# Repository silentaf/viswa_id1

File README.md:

# VisionAid: Vishwakarma Awards 2026–27 (Team SVNIT)

A chest-worn, fully offline navigation aid for blind and low-vision users that **adds head-level-obstacle and drop-off warnings to the white cane**.
- An **FPGA safety island** (Tang Nano 9K) keeps the alert path running even if the AI computer fails.
- An on-device AI layer (Raspberry Pi 5) names hazards and reads text aloud.

**Stage 2: Design Development.** This repository holds the design files. Nothing has been fabricated yet. Every number is labelled *target*, *calculated*, *simulated*, *cited* or *measured on the development laptop* (Pi software, not a Pi 5); none is a measurement on VisionAid hardware.

| Path | Contents |
|---|---|
| [`VisionAid_Proposal_v2.md`](VisionAid_Proposal_v2.md) | Design specification v2: the Stage 1 proposal corrected, with every change explained |
| [`IMPLEMENTATION_PLAN.md`](IMPLEMENTATION_PLAN.md) | Stage 2 plan, gates, slide map, checklist |
| [`design/electronics/`](design/electronics/) | KiCad 9 carrier board: schematic, PCB, Gerbers, BOM, STEP (ERC 0 / DRC 0) |
| [`design/fpga/`](design/fpga/) | Verilog safety island, testbench (all tests pass), waveforms, Yosys utilisation |
| [`design/cad/`](design/cad/) | FreeCAD parametric chest pod, STEP/STL, renders, mount FEA |
| [`design/bom/`](design/bom/) | Prototype BOM and power budget (xlsx) |

All design files are generated by the scripts in each folder (`scripts/`), so every design decision is written down and reproducible. See [`design/README.md`](design/README.md) for the tools and how to open each file.

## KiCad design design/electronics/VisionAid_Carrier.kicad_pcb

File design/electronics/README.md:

# VisionAid Carrier Board: Electronics Design (v0.1, design stage)

**Status (8 Oct 2026):**
- **Designed and verified in KiCad 9:** ERC 0 violations; DRC 0 violations; 0 unconnected; schematic ↔ PCB parity 0 issues.
- **Not fabricated or tested yet.** Every number below is a design value or target, not a measurement.

## What this board does

It is the **interface and safety-island board** that sits on top of the Raspberry Pi 5 in the chest pod.

| Block | Parts | Why it is designed this way |
|---|---|---|
| **FPGA safety island** | U1 Sipeed Tang Nano 9K (GW1NR-9, 27 MHz) on 2 × 24 sockets | Times all 3 ultrasonic echoes **in parallel** and drives the motors **without the Pi**. If Linux or the AI crashes, obstacle alerts continue (watchdog on `PI_HB`). Only **3.3 V-bank pins** on the left header are used; the right-header pins marked `_1V8` are on a 1.8 V bank and are unused. |
| **Pi link** | J1 2 × 20 header → 40-way IDC ribbon → Pi GPIO | UART (GPIO14/15) for status and config, GPIO17 = heartbeat to the FPGA, GPIO27 = fault from the FPGA, I²C (GPIO2/3) for the IMU. |
| **Power** | F1 500 mA PTC, U2 AMS1117-3.3, C1–C5, D1 SS14 | 5 V comes from the Pi header (the Pi is powered by a BIS-certified USB-C power bank). The PTC protects the Pi's 5 V rail if this board shorts. A separate 3.3 V regulator means the Pi's 3.3 V pins (1, 17) are deliberately **not** used. D1 stops back-feed when the Tang Nano's own USB-C is plugged in for programming. |
| **Sensors** | J2–J4 RCWL-1601 ultrasonic (left, right, head-level), J5 TF-Luna LiDAR (drop-offs), J8 MPU-6050 IMU | RCWL-1601 works at 3.3 V, so there is no level shifting. The TF-Luna takes 5 V but has 3.3 V UART logic. 100 Ω series resistors (R7–R14) limit fault current and ringing on the cables. |
| **Haptics and alarm** | Q1–Q3 AO3400A, R1–R6, D2–D4, J6/J7 coin motors, BZ1 buzzer | Logic-level MOSFETs (V_GS(th) ≤ 1.45 V) are switched directly by the FPGA's 3.3 V PWM. 100 kΩ pull-downs keep the motors off while the FPGA boots. Flyback diodes protect the MOSFETs. The motors (3 V coin ERMs) run from +3V3. |
| **Buttons** | J9 (READ = OCR, MODE, QUIET), R15–R17 10 k pull-ups, C7–C9 100 nF | 10 k × 100 nF ≈ 1 ms RC filter, plus digital debounce in the FPGA. |
| **Test points** | TP1–TP6 (+5V, +3V3, GND, US_L_ECHO, MOT_L_G, PI_HB) | For the Stage 3 logic-analyser measurement of **echo → motor-on latency** and for power checks. |

## FPGA pin map (Tang Nano 9K, 3.3 V banks only)

| Signal | FPGA pin | Signal | FPGA pin |
|---|---|---|---|
| US_L_TRIG / ECHO | 25 / 26 | PI_TXD (FPGA RX) / PI_RXD (FPGA TX) | 40 / 35 |
| US_R_TRIG / ECHO | 27 / 28 | PI_HB (heartbeat in) | 41 |
| US_H_TRIG / ECHO | 29 / 30 | FPGA_FAULT_N (out to Pi) | 42 |
| LIDAR_TX / LIDAR_RX | 33 / 34 | MOT_L_PWM / MOT_R_PWM / BUZZ_EN | 51 / 53 / 54 |
| Clock 27 MHz (on module) | 52 | BTN_READ / MODE / QUIET | 55 / 56 / 57 |

Source: the Sipeed Tang Nano 9K official pin map (wiki.sipeed.com).

## PCB

- **Outline:** 85 × 56 mm, 2 layers, 1.6 mm FR-4. It has the **same outline and M2.5 mounting holes as the Raspberry Pi 5**, and is stacked above the Pi on **20 mm standoffs**. Those clear the Pi's USB/Ethernet jacks and the active cooler; a standard HAT would hit them.
- **Layout:**
  - The Tang Nano sits on 8.5 mm sockets, with its USB-C flush at the right edge for programming.
  - Low-profile SMD parts sit **under** the module, between the socket rows.
  - Sensor connectors are on the bottom edge (cables exit downward towards the sensor windows). Buttons, IMU and motor connectors are on the left edge.
- **Track rules:**
  - 5 V and GND: 0.5 mm.
  - +3V3: 0.3 mm (about 250 mA total load).
  - Signals: 0.25 mm (minimum 0.15 mm, where the router necks down at pads).
  - Clearance 0.2 mm; vias 0.6/0.3 mm.
  - GND pours on both layers.
- **Routing:** FreeRouting v2.5.0 completed 100 %, with 0 violations.

## How the files are produced (reproducible)

All files are generated from scripts so every design decision is written down:

```
tools/kicad.sh python design/electronics/scripts/gen_library.py    # Tang Nano symbol + footprint
python3 design/electronics/scripts/gen_schematic.py                # schematic (.kicad_sch)
tools/kicad.sh kicad-cli sch export netlist -o design/electronics/VisionAid_Carrier.net design/electronics/VisionAid_Carrier.kicad_sch
tools/kicad.sh python design/electronics/scripts/gen_pcb.py        # outline, placement, nets
tools/kicad.sh python design/electronics/scripts/route_pcb.py      # FreeRouting + GND pours
```

Open the project in the KiCad GUI with `tools/kicad.sh kicad design/electronics/VisionAid_Carrier.kicad_pro`.

## Outputs (`outputs/`)

| File | Contents |
|---|---|
| `VisionAid_Carrier_schematic.pdf` / `.svg` | Schematic |
| `VisionAid_Carrier_pcb_top.pdf` / `_bottom.pdf` | Copper and silkscreen plots |
| `gerbers/` | Fabrication files (Gerber X2 + Excellon drill + drill map) |
| `VisionAid_Carrier_BOM.csv` | Bill of materials (on-board parts) |
| `VisionAid_Carrier_pos.csv` | Pick-and-place positions |
| `VisionAid_Carrier.step` | 3D model for the enclosure CAD |
| `pcb_3d_top.png` / `pcb_3d_iso.png` | Board renders with component 3D models (Tang Nano 9K: simplified model in `3d/`) |
| `ERC_report.txt` / `DRC_report.txt` | Verification reports |

## Not on the PCB BOM (buy separately in Stage 3)

- 2 × 1×24 female headers (2.54 mm, 8.5 mm tall) for the Tang Nano.
- 40-way IDC ribbon cable with 2 sockets (≈ 10 cm).
- 4 × M2.5 × 20 mm standoffs and screws.
- JST-XH housings and crimps.
- The sensors, motors and buttons themselves (see the implementation plan, §5).

## Open items before fabrication (Stage 3)

1. **Measure the Tang Nano 9K header row spacing with calipers.** The footprint uses 22.86 mm (0.9″), taken from a community footprint, not an official drawing.
2. Confirm the ribbon length and the standoff height against the enclosure CAD.
3. Check the AMS1117 dropout and temperature at the real load: 5 V → 3.3 V at ~250 mA ≈ 0.43 W in SOT-223.
4. Review the board in the KiCad GUI: tidy silkscreen, then re-run DRC.

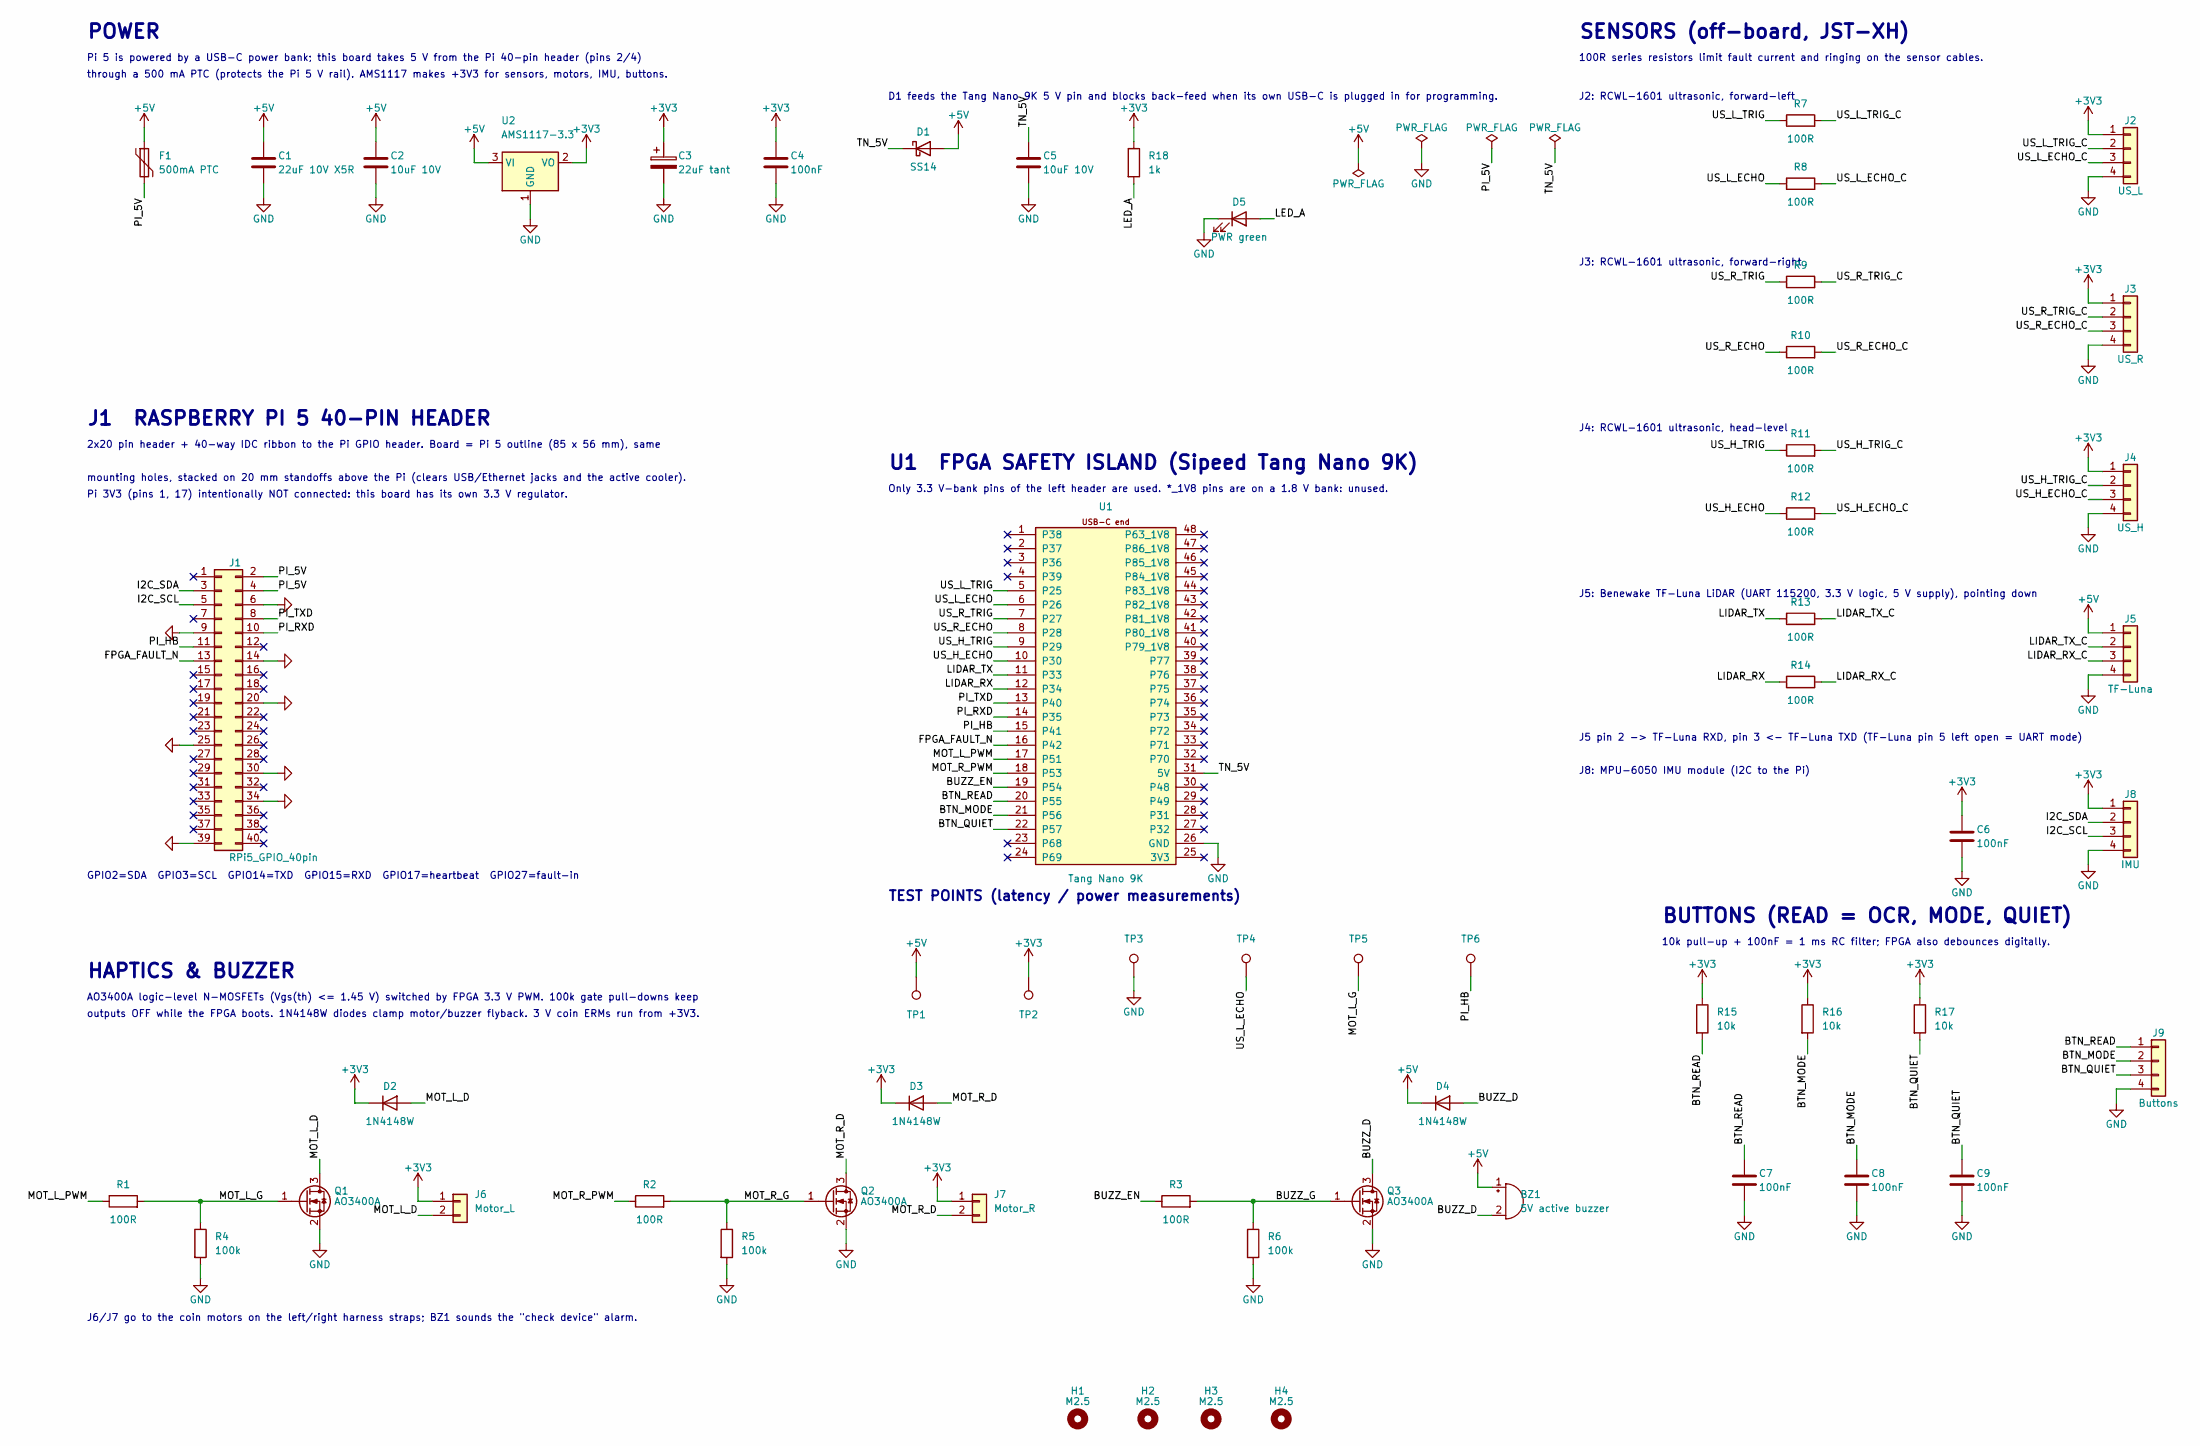
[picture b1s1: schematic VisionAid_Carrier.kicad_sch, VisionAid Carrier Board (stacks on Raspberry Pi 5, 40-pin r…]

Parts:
BZ1: 5V active buzzer; Buzzer_12x9.5RM7.6; MPN 12 mm 5 V active buzzer
C1: 22uF 10V X5R; C_1206_3216Metric
C2, C5: 10uF 10V; C_0805_2012Metric
C3: 22uF tant; CP_EIA-3528-21_Kemet-B
C4, C6, C7, C8, C9: 100nF; C_0603_1608Metric
D1: SS14; D_SMA; MPN SS14
D2, D3, D4: 1N4148W; D_SOD-123; MPN 1N4148W
D5: PWR green; LED_0603_1608Metric
F1: 500mA PTC; Fuse_1206_3216Metric; MPN 1206L050 / equivalent
H1, H2, H3, H4: M2.5; MountingHole_2.7mm_M2.5
J1: RPi5_GPIO_40pin; PinHeader_2x20_P2.54mm_Vertical
J2: US_L; JST_XH_B4B-XH-A_1x04_P2.50mm_Vertical; MPN JST B4B-XH-A
J3: US_R; JST_XH_B4B-XH-A_1x04_P2.50mm_Vertical; MPN JST B4B-XH-A
J4: US_H; JST_XH_B4B-XH-A_1x04_P2.50mm_Vertical; MPN JST B4B-XH-A
J5: TF-Luna; JST_XH_B4B-XH-A_1x04_P2.50mm_Vertical; MPN JST B4B-XH-A
J6: Motor_L; JST_XH_B2B-XH-A_1x02_P2.50mm_Vertical; MPN JST B2B-XH-A
J7: Motor_R; JST_XH_B2B-XH-A_1x02_P2.50mm_Vertical; MPN JST B2B-XH-A
J8: IMU; JST_XH_B4B-XH-A_1x04_P2.50mm_Vertical; MPN JST B4B-XH-A
J9: Buttons; JST_XH_B4B-XH-A_1x04_P2.50mm_Vertical; MPN JST B4B-XH-A
Q1, Q2, Q3: AO3400A; SOT-23; MPN AO3400A
R1, R2, R3, R7, R8, R9, R10, R11, R12, R13, R14: 100R; R_0603_1608Metric
R4, R5, R6: 100k; R_0603_1608Metric
R15, R16, R17: 10k; R_0603_1608Metric
R18: 1k; R_0603_1608Metric
TP1: +5V; TestPoint_Pad_D1.5mm
TP2: +3V3; TestPoint_Pad_D1.5mm
TP3: GND; TestPoint_Pad_D1.5mm
TP4: US_L_ECHO; TestPoint_Pad_D1.5mm
TP5: MOT_L_G; TestPoint_Pad_D1.5mm
TP6: PI_HB; TestPoint_Pad_D1.5mm
U1: Tang Nano 9K; TangNano9K_Module; MPN Sipeed Tang Nano 9K
U2: AMS1117-3.3; SOT-223-3_TabPin2; MPN AMS1117-3.3

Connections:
+3V3: C3.1, C4.1, C6.1, D2.1 (K), D3.1 (K), J2.1, J3.1, J4.1, J6.1, J7.1, J8.1, R15.1, R16.1, R17.1, R18.1, TP2.1, U2.2 (VO)
+5V: BZ1.1 (+), C1.1, C2.1, D1.2 (A), D4.1 (K), F1.1, J5.1, TP1.1, U2.3 (VI)
/BTN_MODE: C8.1, J9.2, R16.2, U1.21 (P56)
/BTN_QUIET: C9.1, J9.3, R17.2, U1.22 (P57)
/BTN_READ: C7.1, J9.1, R15.2, U1.20 (P55)
/BUZZ_D: BZ1.2 (-), D4.2 (A), Q3.3 (D)
/BUZZ_EN: R3.1, U1.19 (P54)
/BUZZ_G: Q3.1 (G), R3.2, R6.1
/FPGA_FAULT_N: J1.13, U1.16 (P42)
/I2C_SCL: J1.5, J8.3
/I2C_SDA: J1.3, J8.2
/LED_A: D5.2 (A), R18.2
/LIDAR_RX: R14.1, U1.12 (P34)
/LIDAR_RX_C: J5.3, R14.2
/LIDAR_TX: R13.1, U1.11 (P33)
/LIDAR_TX_C: J5.2, R13.2
/MOT_L_D: D2.2 (A), J6.2, Q1.3 (D)
/MOT_L_G: Q1.1 (G), R1.2, R4.1, TP5.1
/MOT_L_PWM: R1.1, U1.17 (P51)
/MOT_R_D: D3.2 (A), J7.2, Q2.3 (D)
/MOT_R_G: Q2.1 (G), R2.2, R5.1
/MOT_R_PWM: R2.1, U1.18 (P53)
/PI_5V: F1.2, J1.2, J1.4
/PI_HB: J1.11, TP6.1, U1.15 (P41)
/PI_RXD: J1.10, U1.14 (P35)
/PI_TXD: J1.8, U1.13 (P40)
/TN_5V: C5.1, D1.1 (K), U1.31 (5V)
/US_H_ECHO: R12.1, U1.10 (P30)
/US_H_ECHO_C: J4.3, R12.2
/US_H_TRIG: R11.1, U1.9 (P29)
/US_H_TRIG_C: J4.2, R11.2
/US_L_ECHO: R8.1, TP4.1, U1.6 (P26)
/US_L_ECHO_C: J2.3, R8.2
/US_L_TRIG: R7.1, U1.5 (P25)
/US_L_TRIG_C: J2.2, R7.2
/US_R_ECHO: R10.1, U1.8 (P28)
/US_R_ECHO_C: J3.3, R10.2
/US_R_TRIG: R9.1, U1.7 (P27)
/US_R_TRIG_C: J3.2, R9.2
GND: C1.2, C2.2, C3.2, C4.2, C5.2, C6.2, C7.2, C8.2, C9.2, D5.1 (K), J1.6, J1.9, J1.14, J1.20, J1.25, J1.30, J1.34, J1.39, J2.4, J3.4, J4.4, J5.4, J8.4, J9.4, Q1.2 (S), Q2.2 (S), Q3.2 (S), R4.2, R5.2, R6.2, TP3.1, U1.26 (GND), U2.1 (GND)

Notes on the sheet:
POWER
Pi 5 is powered by a USB-C power bank; this board takes 5 V from the Pi 40-pin header (pins 2/4)
through a 500 mA PTC (protects the Pi 5 V rail). AMS1117 makes +3V3 for sensors, motors, IMU, buttons.
D1 feeds the Tang Nano 9K 5 V pin and blocks back-feed when its own USB-C is plugged in for programming.
J1 RASPBERRY PI 5 40-PIN HEADER
2x20 pin header + 40-way IDC ribbon to the Pi GPIO header. Board = Pi 5 outline (85 x 56 mm), same
mounting holes, stacked on 20 mm standoffs above the Pi (clears USB/Ethernet jacks and the active cooler).
Pi 3V3 (pins 1, 17) intentionally NOT connected: this board has its own 3.3 V regulator.
GPIO2=SDA GPIO3=SCL GPIO14=TXD GPIO15=RXD GPIO17=heartbeat GPIO27=fault-in
U1 FPGA SAFETY ISLAND (Sipeed Tang Nano 9K)
Only 3.3 V-bank pins of the left header are used. *_1V8 pins are on a 1.8 V bank: unused.
SENSORS (off-board, JST-XH)
100R series resistors limit fault current and ringing on the sensor cables.
J2: RCWL-1601 ultrasonic, forward-left
J3: RCWL-1601 ultrasonic, forward-right
J4: RCWL-1601 ultrasonic, head-level
J5: Benewake TF-Luna LiDAR (UART 115200, 3.3 V logic, 5 V supply), pointing down
J5 pin 2 -> TF-Luna RXD, pin 3 <- TF-Luna TXD (TF-Luna pin 5 left open = UART mode)
J8: MPU-6050 IMU module (I2C to the Pi)
HAPTICS & BUZZER
AO3400A logic-level N-MOSFETs (Vgs(th) <= 1.45 V) switched by FPGA 3.3 V PWM. 100k gate pull-downs keep
outputs OFF while the FPGA boots. 1N4148W diodes clamp motor/buzzer flyback. 3 V coin ERMs run from +3V3.
J6/J7 go to the coin motors on the left/right harness straps; BZ1 sounds the "check device" alarm.
BUTTONS (READ = OCR, MODE, QUIET)
10k pull-up + 100nF = 1 ms RC filter; FPGA also debounces digitally.
TEST POINTS (latency / power measurements)

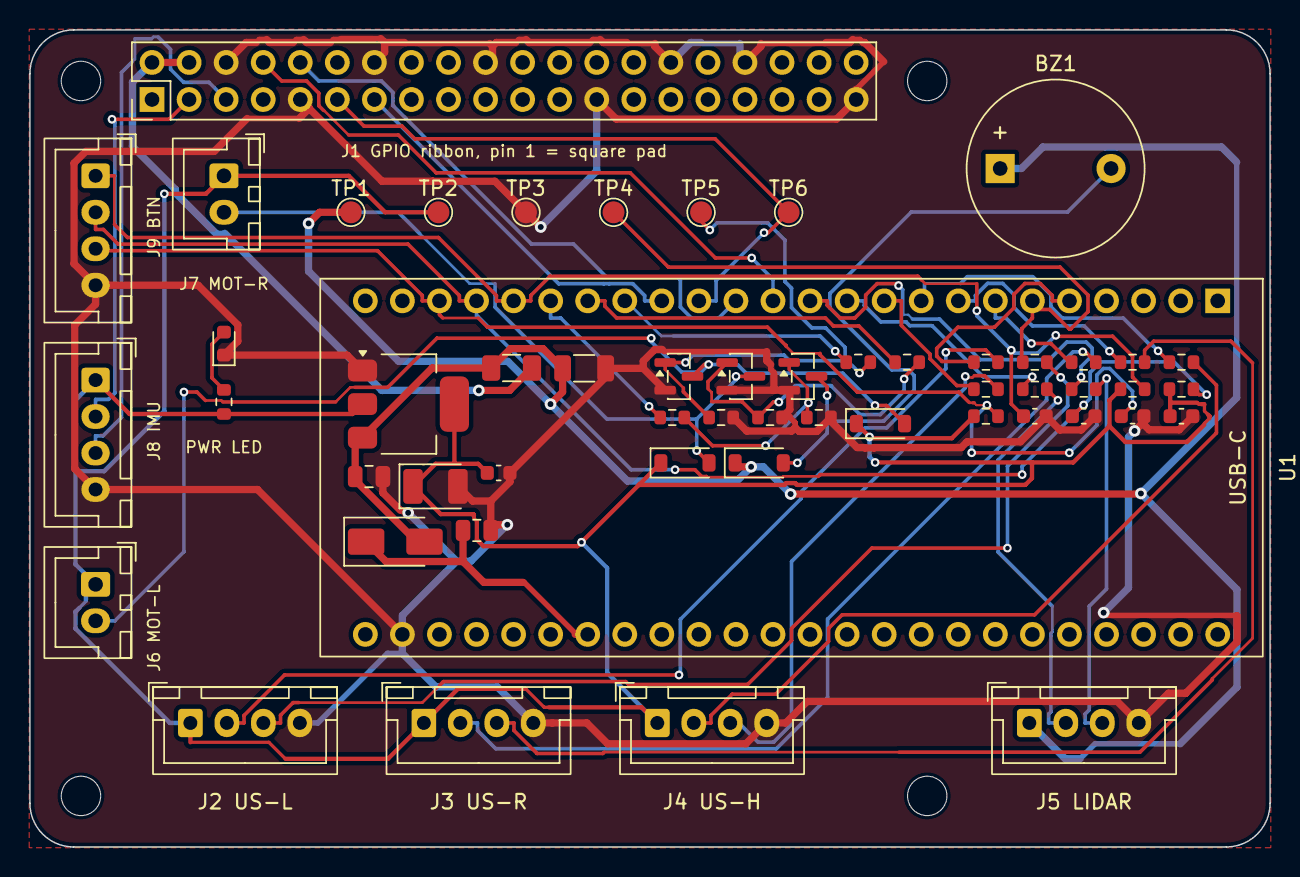
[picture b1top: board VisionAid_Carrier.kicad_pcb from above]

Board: 2 copper layers, 85.0 x 56.0 mm, 58 parts (0 on the bottom side), 40 nets.

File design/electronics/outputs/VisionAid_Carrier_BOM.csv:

"Refs","Value","Footprint","MPN","Qty"
"BZ1","5V active buzzer","Buzzer_Beeper:Buzzer_12x9.5RM7.6","12 mm 5 V active buzzer","1"
"C1","22uF 10V X5R","Capacitor_SMD:C_1206_3216Metric","","1"
"C2,C5","10uF 10V","Capacitor_SMD:C_0805_2012Metric","","2"
"C3","22uF tant","Capacitor_Tantalum_SMD:CP_EIA-3528-21_Kemet-B","","1"
"C4,C6,C7,C8,C9","100nF","Capacitor_SMD:C_0603_1608Metric","","5"
"D1","SS14","Diode_SMD:D_SMA","SS14","1"
"D2,D3,D4","1N4148W","Diode_SMD:D_SOD-123","1N4148W","3"
"D5","PWR green","LED_SMD:LED_0603_1608Metric","","1"
"F1","500mA PTC","Fuse:Fuse_1206_3216Metric","1206L050 / equivalent","1"
"J1","RPi5_GPIO_40pin","Connector_PinHeader_2.54mm:PinHeader_2x20_P2.54mm_Vertical","","1"
"J2","US_L","Connector_JST:JST_XH_B4B-XH-A_1x04_P2.50mm_Vertical","JST B4B-XH-A","1"
"J3","US_R","Connector_JST:JST_XH_B4B-XH-A_1x04_P2.50mm_Vertical","JST B4B-XH-A","1"
"J4","US_H","Connector_JST:JST_XH_B4B-XH-A_1x04_P2.50mm_Vertical","JST B4B-XH-A","1"
"J5","TF-Luna","Connector_JST:JST_XH_B4B-XH-A_1x04_P2.50mm_Vertical","JST B4B-XH-A","1"
"J6","Motor_L","Connector_JST:JST_XH_B2B-XH-A_1x02_P2.50mm_Vertical","JST B2B-XH-A","1"
"J7","Motor_R","Connector_JST:JST_XH_B2B-XH-A_1x02_P2.50mm_Vertical","JST B2B-XH-A","1"
"J8","IMU","Connector_JST:JST_XH_B4B-XH-A_1x04_P2.50mm_Vertical","JST B4B-XH-A","1"
"J9","Buttons","Connector_JST:JST_XH_B4B-XH-A_1x04_P2.50mm_Vertical","JST B4B-XH-A","1"
"Q1,Q2,Q3","AO3400A","Package_TO_SOT_SMD:SOT-23","AO3400A","3"
"R1,R2,R3,R7,R8,R9,R10,R11,R12,R13,R14","100R","Resistor_SMD:R_0603_1608Metric","","11"
"R4,R5,R6","100k","Resistor_SMD:R_0603_1608Metric","","3"
"R15,R16,R17","10k","Resistor_SMD:R_0603_1608Metric","","3"
"R18","1k","Resistor_SMD:R_0603_1608Metric","","1"
"U1","Tang Nano 9K","VisionAid:TangNano9K_Module","Sipeed Tang Nano 9K","1"
"U2","AMS1117-3.3","Package_TO_SOT_SMD:SOT-223-3_TabPin2","AMS1117-3.3","1"

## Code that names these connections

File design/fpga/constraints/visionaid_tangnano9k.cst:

// VisionAid safety island - Tang Nano 9K (GW1NR-LV9QN88PC6/I5) physical constraints.
// Pin numbers from the Sipeed Tang Nano 9K pin map; all user I/O on the 3.3 V banks (left header).
IO_LOC "clk" 52;
IO_PORT "clk" IO_TYPE=LVCMOS33 PULL_MODE=UP;
IO_LOC "rst_n" 4;
IO_PORT "rst_n" PULL_MODE=UP;  // on-board button S1
IO_LOC "us_trig[0]" 25;
IO_PORT "us_trig[0]" IO_TYPE=LVCMOS33 DRIVE=8;
IO_LOC "us_echo[0]" 26;
IO_PORT "us_echo[0]" IO_TYPE=LVCMOS33 PULL_MODE=DOWN;
IO_LOC "us_trig[1]" 27;
IO_PORT "us_trig[1]" IO_TYPE=LVCMOS33 DRIVE=8;
IO_LOC "us_echo[1]" 28;
IO_PORT "us_echo[1]" IO_TYPE=LVCMOS33 PULL_MODE=DOWN;
IO_LOC "us_trig[2]" 29;
IO_PORT "us_trig[2]" IO_TYPE=LVCMOS33 DRIVE=8;
IO_LOC "us_echo[2]" 30;
IO_PORT "us_echo[2]" IO_TYPE=LVCMOS33 PULL_MODE=DOWN;
IO_LOC "lidar_tx" 33;
IO_PORT "lidar_tx" IO_TYPE=LVCMOS33;
IO_LOC "lidar_rx" 34;
IO_PORT "lidar_rx" IO_TYPE=LVCMOS33 PULL_MODE=UP;
IO_LOC "pi_txd" 40;
IO_PORT "pi_txd" IO_TYPE=LVCMOS33 PULL_MODE=UP;  // from Pi GPIO14
IO_LOC "pi_rxd" 35;
IO_PORT "pi_rxd" IO_TYPE=LVCMOS33;  // to Pi GPIO15
IO_LOC "pi_hb" 41;
IO_PORT "pi_hb" IO_TYPE=LVCMOS33 PULL_MODE=DOWN;  // from Pi GPIO17
IO_LOC "fpga_fault_n" 42;
IO_PORT "fpga_fault_n" IO_TYPE=LVCMOS33;  // to Pi GPIO27
IO_LOC "mot_l" 51;
IO_PORT "mot_l" IO_TYPE=LVCMOS33 DRIVE=8;
IO_LOC "mot_r" 53;
IO_PORT "mot_r" IO_TYPE=LVCMOS33 DRIVE=8;
IO_LOC "buzz" 54;
IO_PORT "buzz" IO_TYPE=LVCMOS33 DRIVE=8;
IO_LOC "btn_read_n" 55;
IO_PORT "btn_read_n" IO_TYPE=LVCMOS33 PULL_MODE=UP;
IO_LOC "btn_mode_n" 56;
IO_PORT "btn_mode_n" IO_TYPE=LVCMOS33 PULL_MODE=UP;
IO_LOC "btn_quiet_n" 57;
IO_PORT "btn_quiet_n" IO_TYPE=LVCMOS33 PULL_MODE=UP;
IO_LOC "led_n[0]" 10;
IO_LOC "led_n[1]" 11;
IO_LOC "led_n[2]" 13;
IO_LOC "led_n[3]" 14;
IO_LOC "led_n[4]" 15;
IO_LOC "led_n[5]" 16;
